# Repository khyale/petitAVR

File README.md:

This repo contains the main files of the project 'petitAVR'. It is a small circuit board designed for the microcontroller (MCU) Atmega328P, which the most important pins have been available to connect others circuits/peripherals such as sensors, communication devices, displays, etc.

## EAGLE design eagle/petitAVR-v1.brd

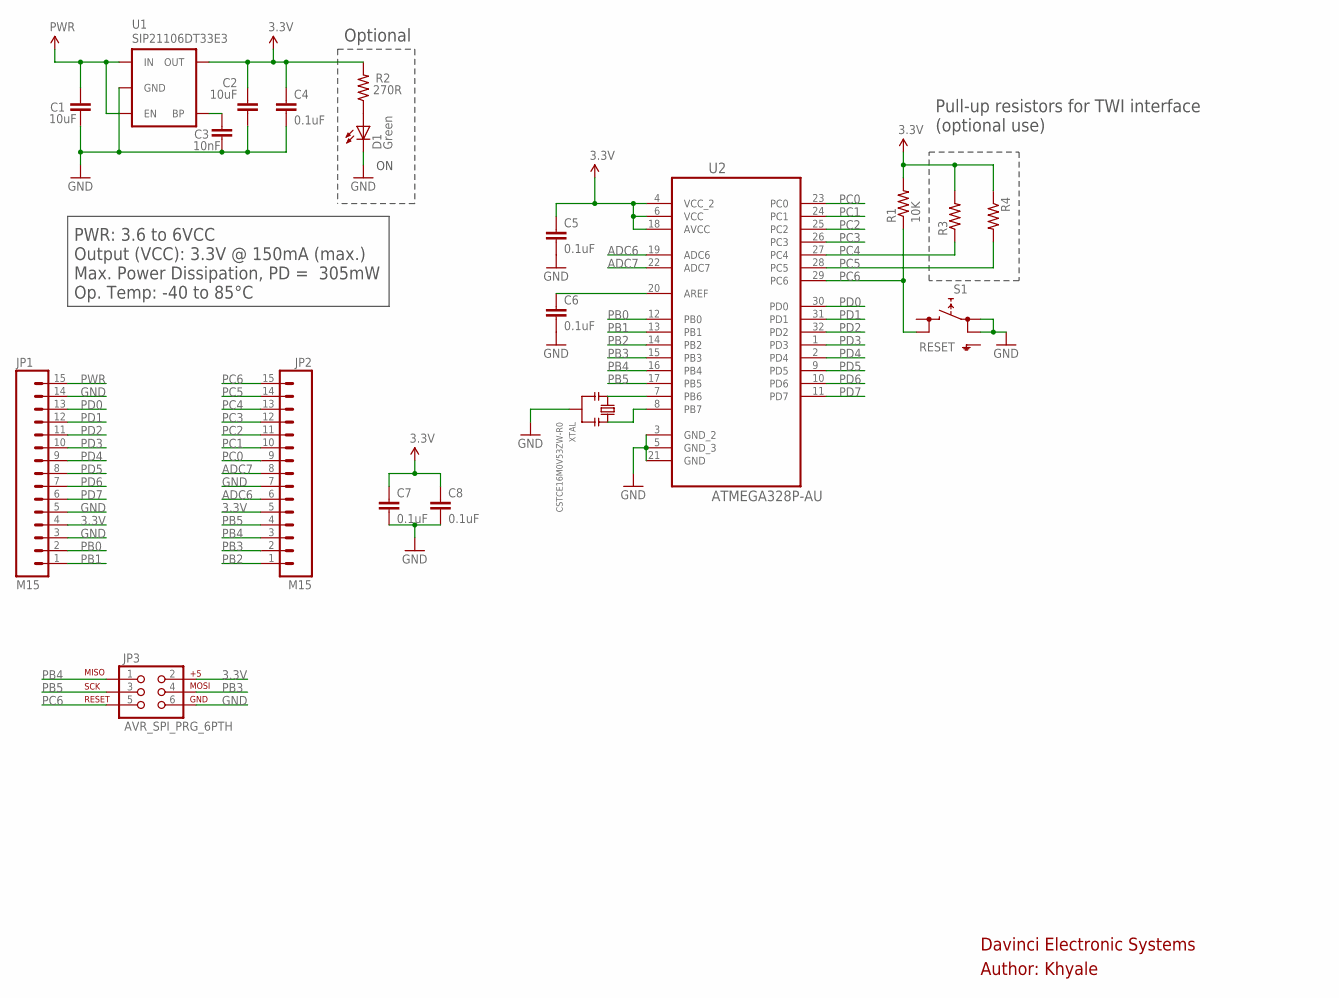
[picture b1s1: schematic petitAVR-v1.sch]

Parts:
C1, C2: 10uF; 0805; MPN LMK212AB7106MG-T
C3: 10nF; 0805; MPN VJ0805Y103JXQCW1BC
C4, C5, C6, C7, C8: 0.1uF; 0603-CAP; MPN VJ0603Y104KXJCW1BC
D1: Green; LED-0603; MPN VLMG1300-GS08
JP1, JP2: M15; 1X15; MPN 22-28-4151
JP3: AVR_SPI_PRG_6PTH; 2X3; MPN 103328-3
R1: 10K; 0603-RES; MPN ERJ-3EKF1002V
R2: 270R; 0805; MPN ERJ-6GEYJ271V
R3: RESISTOR0603-RES; 0603-RES
R4: RESISTOR0603; 0603-RES
S1: RESET; SKHMPXE010; MPN FSM1LPATR
U1: SIP21106DT33E3; SOT23-5; MPN SIP21106DT-33-E3
U2: ATMEGA328P-AU; QFP80P900X900X120-32N
XTAL: CSTCE16M0V53ZW-R0; CSTCE_V; MPN CSTCE16M0V53ZW-R0

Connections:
3.3V: C2.2, C4.1, C5.1, C7.1, C8.1, JP1.4, JP2.5, JP3.2, R1.2, R2.2, R3.2, R4.1, U1.5 (OUT), U2.4 (VCC_2), U2.6 (VCC), U2.18 (AVCC)
ADC6: JP2.6, U2.19 (ADC6)
ADC7: JP2.8, U2.22 (ADC7)
GND: C1.1, C2.1, C3.1, C4.2, C5.2, C6.2, C7.2, C8.2, D1.C, JP1.3, JP1.5, JP1.14, JP2.7, JP3.6, S1.1 (1.1), S1.2 (1.2), U1.2 (GND), U2.3 (GND_2), U2.5 (GND_3), U2.21 (GND), XTAL.P2
unnamed: D1.A, R2.1
unnamed: U2.7 (PB6), XTAL.P3
unnamed: U2.8 (PB7), XTAL.P1
unnamed: C3.2, U1.4 (BP)
unnamed: C6.1, U2.20 (AREF)
PB0: JP1.2, U2.12 (PB0)
PB1: JP1.1, U2.13 (PB1)
PB2: JP2.1, U2.14 (PB2)
PB3: JP2.2, JP3.4, U2.15 (PB3)
PB4: JP2.3, JP3.1, U2.16 (PB4)
PB5: JP2.4, JP3.3, U2.17 (PB5)
PC0: JP2.9, U2.23 (PC0)
PC1: JP2.10, U2.24 (PC1)
PC2: JP2.11, U2.25 (PC2)
PC3: JP2.12, U2.26 (PC3)
PC4: JP2.13, R3.1, U2.27 (PC4)
PC5: JP2.14, R4.2, U2.28 (PC5)
PC6: JP2.15, JP3.5, R1.1, S1.4 (2.2), U2.29 (PC6)
PD0: JP1.13, U2.30 (PD0)
PD1: JP1.12, U2.31 (PD1)
PD2: JP1.11, U2.32 (PD2)
PD3: JP1.10, U2.1 (PD3)
PD4: JP1.9, U2.2 (PD4)
PD5: JP1.8, U2.9 (PD5)
PD6: JP1.7, U2.10 (PD6)
PD7: JP1.6, U2.11 (PD7)
PWR: C1.2, JP1.15, U1.1 (IN), U1.3 (EN)

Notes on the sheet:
PWR: 3.6 to 6VCC Output (VCC): 3.3V @ 150mA (max.) Max. Power Dissipation, PD = 305mW Op. Temp: -40 to 85°C
Pull-up resistors for TWI interface (optional use)
Davinci Electronic Systems
Optional
Author: Khyale

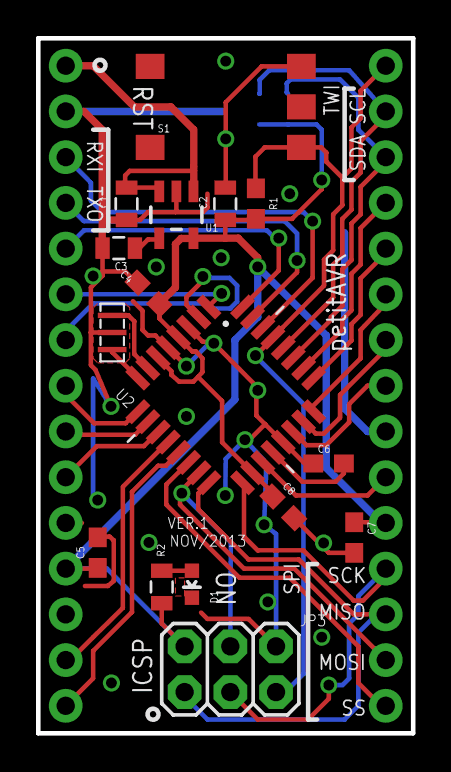
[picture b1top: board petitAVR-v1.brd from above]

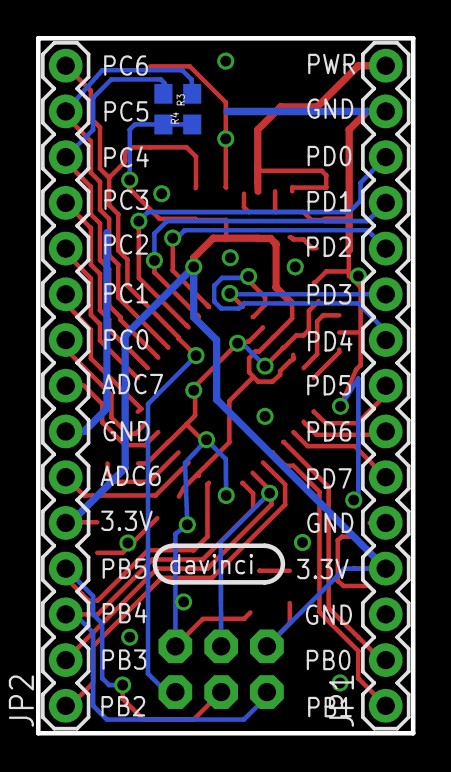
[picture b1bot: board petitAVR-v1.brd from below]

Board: 2 copper layers, 20.8 x 38.6 mm, 20 parts (4 on the bottom side), 31 nets.

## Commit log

2013-11-21 simple description of the project
2014-01-13 Added image of PCB board fabricated by OSH Park

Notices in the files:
parts and their libraries:
SparkFun-PowerIC: Licensing: CC v3.0 Share-Alike You are welcome to use this library for commercial purposes.
